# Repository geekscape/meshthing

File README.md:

meshthing
=========

MeshThing module: Hardware and software repository

Current version is v1.2.

Contents:
----------
-Hardware - Source files for PCB production.

-Software - Source files for testing and use.

-Resources - Additional utilities and documentation.

-Reference - Mostly datasheets.

Pinout:

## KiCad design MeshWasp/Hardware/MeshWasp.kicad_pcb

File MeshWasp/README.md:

meshwasp
=========

MeshWasp breakout: Hardware and software repository

This board hosts a meshthing 802.15.4 radio module and brings a selection of pins to an XBee form factor. It also includes a micro-SD card holder, reset switch, and LEDs for power and SCK signaling.

Current version is v1.0

Contents:
----------
-Hardware - Source files for PCB production.

-Resources - Additional utilities and documentation.

Pinout:

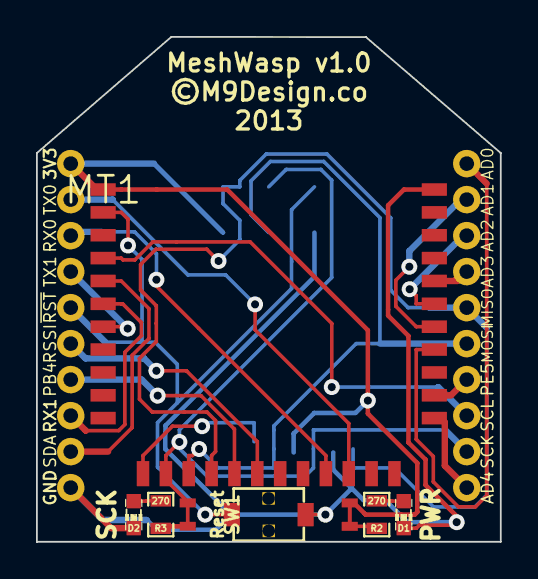
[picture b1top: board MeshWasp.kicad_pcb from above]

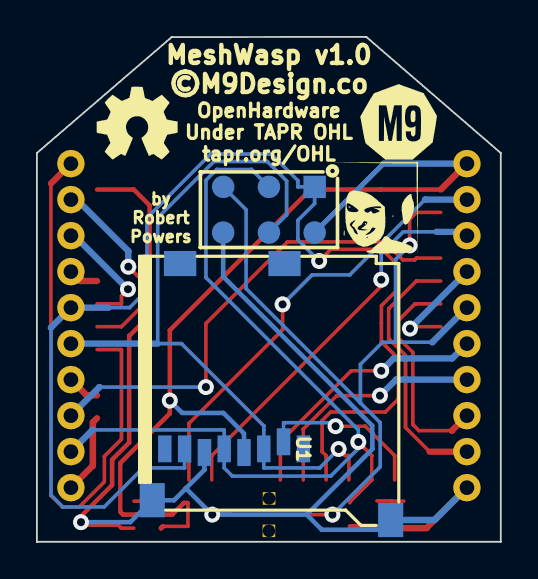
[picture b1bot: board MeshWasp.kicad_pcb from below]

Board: 2 copper layers, 25.8 x 28.1 mm, 14 parts (5 on the bottom side), 25 nets.

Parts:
D1, D2: LED; _MT_LED-0603
G1, G2: LOGO
H2: ICSP; _MC_pin_pad_3x2
MT1: MESHTHING; _MT_CanFootprint-34Pin
R2, R3: 270; _MT_SM0603_Resistor
SJ1, SJ2: SMTJPR; _MW_SMTJumper
SW1: RST; _MT_TC007-TactileSwitch
U1: CONN_MICROSD; _MW_microSD_3M_290805-A
U2: XBEE; _MW_XBee_Board_STD_THPads
VAL: M9Logo-flipped

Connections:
+3.3V: H2.2, MT1.1, SJ1.1, U1.4, U2.1
GND: D1.2, D2.2, H2.6, MT1.34, SW1.2, U1.6, U1.9, U2.10
MISO: H2.1, MT1.15, U1.7, U2.16
MOSI: H2.4, MT1.14, U1.3, U2.15
unnamed: D1.1, R2.2
unnamed: D2.1, R3.2
unnamed: R2.1, SJ1.2
unnamed: R3.1, SJ2.2
PB0/SS: MT1.12, U1.2
PB4: MT1.16, U2.7
PB5: MT1.17, U2.6
PE4: MT1.24, U2.11
PE5: MT1.25, U2.14
PF0: MT1.27, U2.20
PF1: MT1.28, U2.19
PF2: MT1.29, U2.18
PF3-4: MT1.30, U2.17
RX0: MT1.20, U2.3
RX1: MT1.6, U2.8
Reset: H2.5, MT1.2, SW1.1, U2.5
SCK: H2.3, MT1.13, SJ2.1, U1.5, U2.12
SCL: MT1.4, U2.13
SDA: MT1.5, U2.9
TX0: MT1.21, U2.2
TX1: MT1.7, U2.4

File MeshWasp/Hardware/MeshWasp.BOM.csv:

Part	Reference	Value	Package	Manufacturer	MFG. Part No.	Number	Comment	Link	Digikey PartNo.		More Notes/Comments
SMD LED	D1	RED LED	SM0603	Lite-On Inc	LTST-C190KRKT	1	2v/red	http://www.digikey.com/product-detail/en/LTST-C190KRKT/160-1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	160-1436-1-ND		
SMD LED	D2	GREEN LED	SM0603	Lite-On Inc	LTST-C190GKT	1	2v/green	http://www.digikey.com/product-detail/en/LTST-C190GKT/160-11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	160-1183-1-ND		
SMD R	R2/R3	270R	SM0603	Panasonic Electronic Components	ERJ-3GEYJ271V	2	.1W rating	http://www.digikey.com.au/product-detail/en/ERJ-3GEYJ271V/P2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	P270GCT-ND		
Tactile Switch	SW1	Reset	2.9 X 3.9 mm	Well Buying Industrial Co. Ltd.	TC007-BBA	1		http://industry.teema.org.tw/auto/PdtCmpProd_eng.asp?id=2160			2.5mm Tall
uSD Card Connector/Holder	U1	CONN_MICROSD		Amphenol Commercial Products	101-00581-59	1		http://www.digikey.com/product-detail/en/101-00581-59/101-00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	101-00581-59-1-ND		
											
10 Pin 2mm Recepticles	H1/H2	Headers	10 pin x 1 row	SAMTEC	SAMTEC SQT-110-03-L-S	2	Male/female	http://www.samtec.com/ftppub/pdf/sqt_th.pdf

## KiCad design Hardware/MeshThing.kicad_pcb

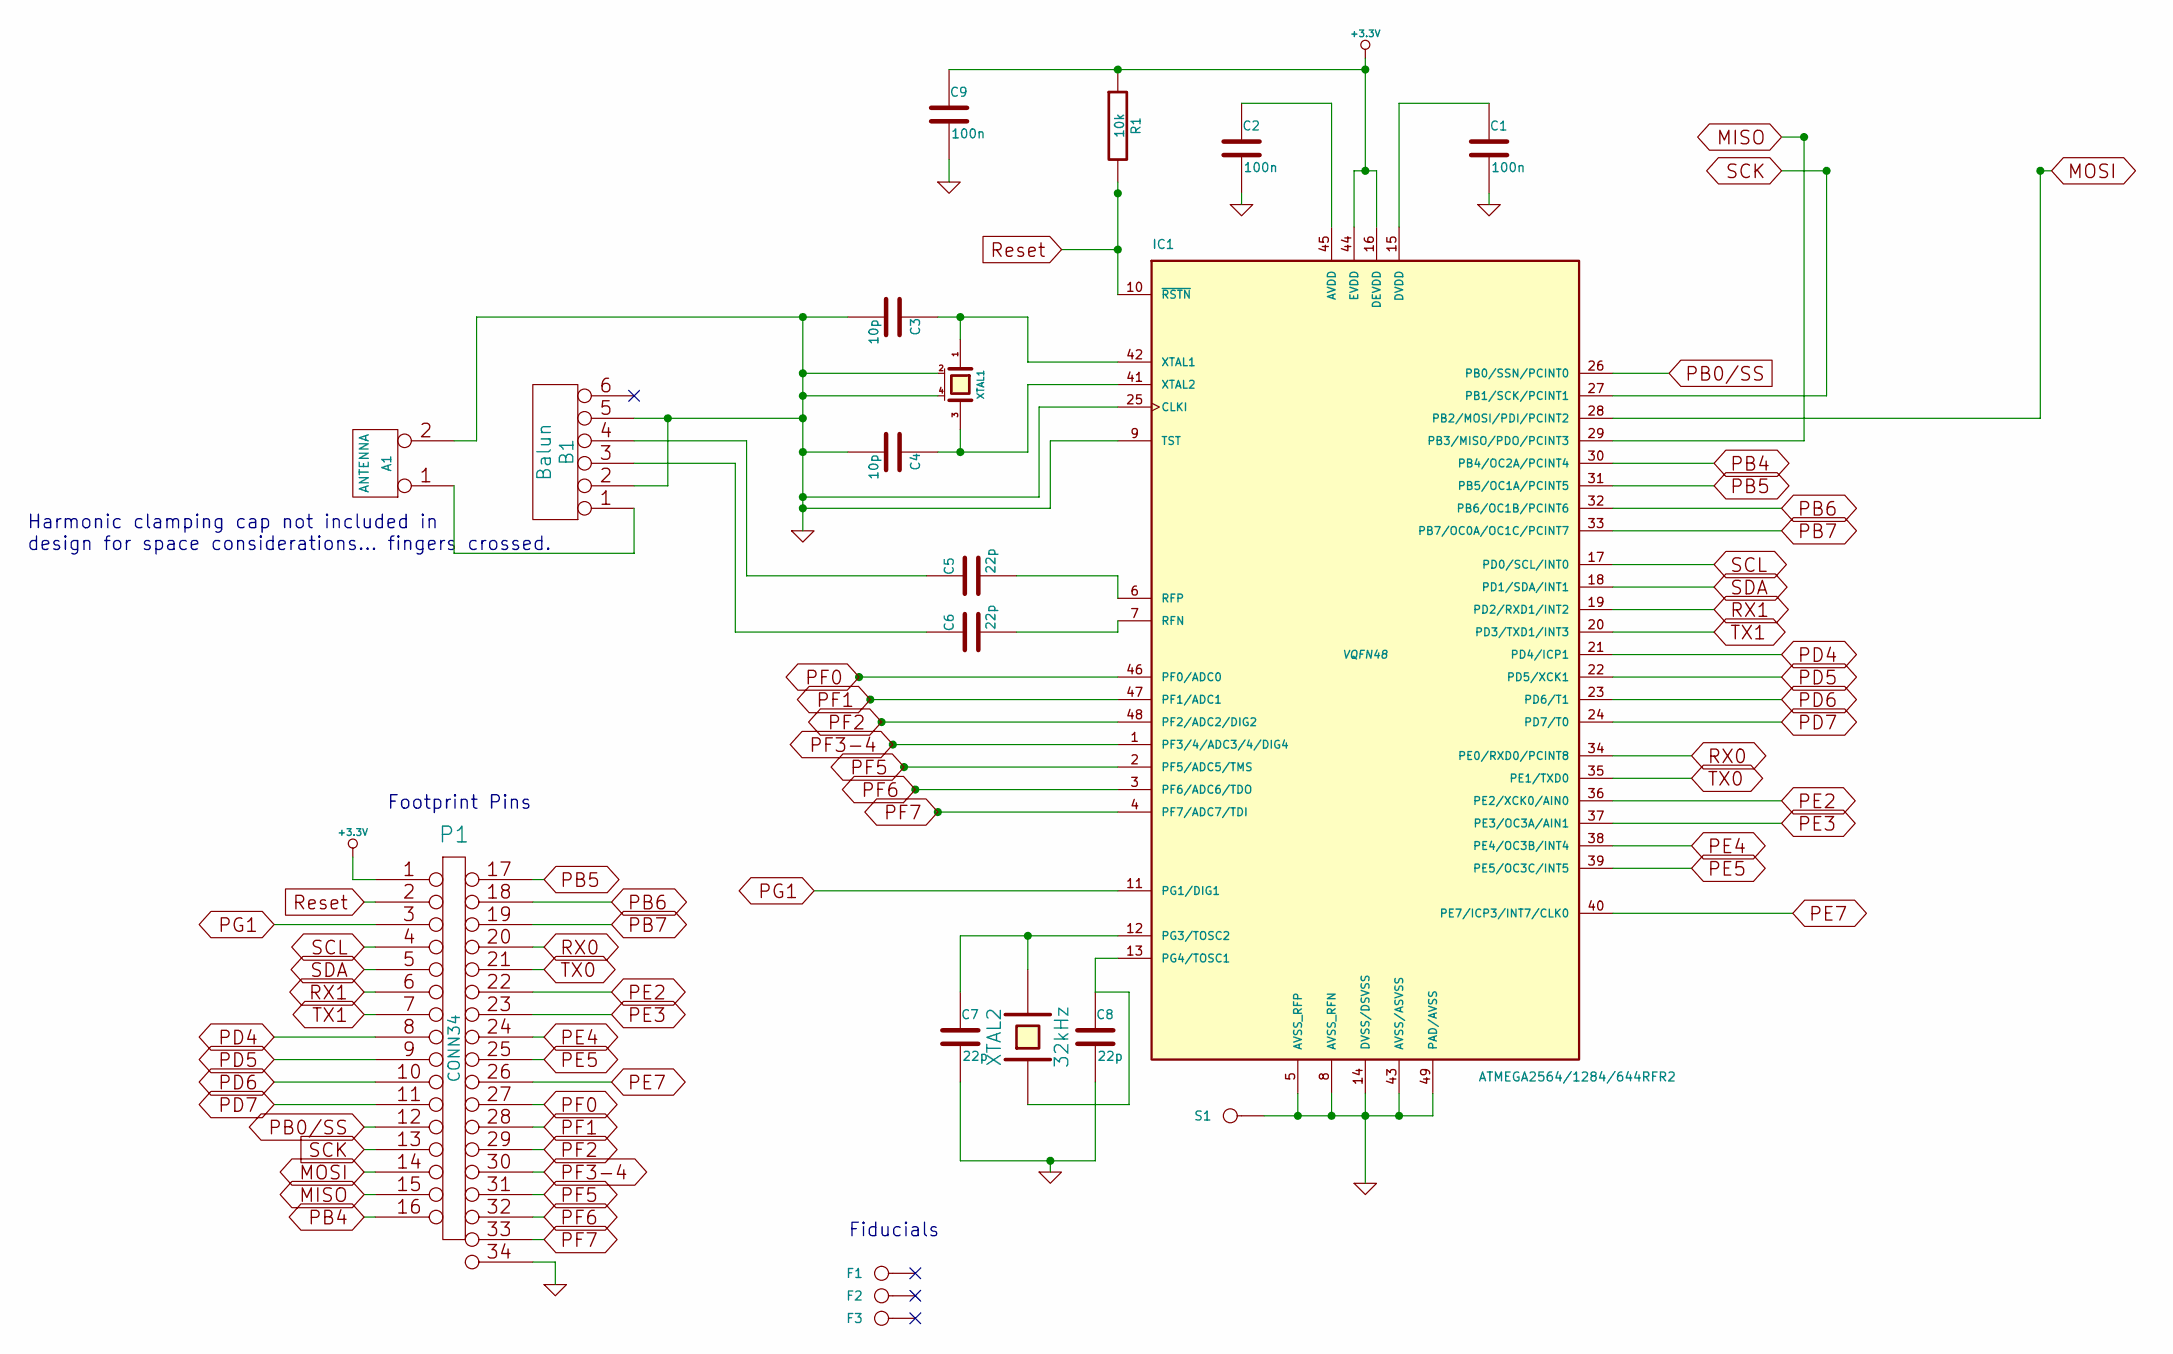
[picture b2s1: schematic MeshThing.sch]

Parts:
A1: ANTENNA
B1: Balun
C1, C2, C9: 100n
C3, C4: 10p
C5, C6, C7, C8: 22p
F1, F2, F3: CONN_1
IC1: ATMEGA2564/1284/644RFR2; VQFN48
P1: CONN34
R1: 10k
S1: RFShield
XTAL1: CRYSTAL_SMD-TSX3225
XTAL2: 32kHz

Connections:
+3.3V: C9.1, IC1.16 (DEVDD), IC1.44 (EVDD), P1.1, R1.1
GND: A1.2 (PM), B1.2, B1.5, C1.2, C2.2, C3.2, C4.2, C7.2, C8.2, C9.2, IC1.5 (AVSS_RFP), IC1.8 (AVSS_RFN), IC1.9 (TST), IC1.14 (DVSS/DSVSS), IC1.25 (CLKI), IC1.43 (AVSS/ASVSS), IC1.49 (PAD/AVSS), P1.34, S1.1, XTAL1.2 (case), XTAL1.4 (case)
MISO: IC1.29 (PB3/MISO/PDO/PCINT3), P1.15
MOSI: IC1.28 (PB2/MOSI/PDI/PCINT2), P1.14
unnamed: A1.1, B1.1
unnamed: B1.3, C6.1
unnamed: B1.4, C5.1
unnamed: C1.1, IC1.15 (DVDD)
unnamed: C2.1, IC1.45 (AVDD)
unnamed: C3.1, IC1.42 (XTAL1), XTAL1.1
unnamed: C4.1, IC1.41 (XTAL2), XTAL1.3
unnamed: C5.2, IC1.6 (RFP)
unnamed: C6.2, IC1.7 (RFN)
unnamed: C7.1, IC1.12 (PG3/TOSC2), XTAL2.2
unnamed: C8.1, IC1.13 (PG4/TOSC1), XTAL2.1
PB0/SS: IC1.26 (PB0/SSN/PCINT0), P1.12
PB4: IC1.30 (PB4/OC2A/PCINT4), P1.16
PB5: IC1.31 (PB5/OC1A/PCINT5), P1.17
PB6: IC1.32 (PB6/OC1B/PCINT6), P1.18
PB7: IC1.33 (PB7/OC0A/OC1C/PCINT7), P1.19
PD4: IC1.21 (PD4/ICP1), P1.8
PD5: IC1.22 (PD5/XCK1), P1.9
PD6: IC1.23 (PD6/T1), P1.10
PD7: IC1.24 (PD7/T0), P1.11
PE2: IC1.36 (PE2/XCK0/AIN0), P1.22
PE3: IC1.37 (PE3/OC3A/AIN1), P1.23
PE4: IC1.38 (PE4/OC3B/INT4), P1.24
PE5: IC1.39 (PE5/OC3C/INT5), P1.25
PE7: IC1.40 (PE7/ICP3/INT7/CLK0), P1.26
PF0: IC1.46 (PF0/ADC0), P1.27
PF1: IC1.47 (PF1/ADC1), P1.28
PF2: IC1.48 (PF2/ADC2/DIG2), P1.29
PF3-4: IC1.1 (PF3/4/ADC3/4/DIG4), P1.30
PF5: IC1.2 (PF5/ADC5/TMS), P1.31
PF6: IC1.3 (PF6/ADC6/TDO), P1.32
PF7: IC1.4 (PF7/ADC7/TDI), P1.33
PG1: IC1.11 (PG1/DIG1), P1.3
RX0: IC1.34 (PE0/RXD0/PCINT8), P1.20
RX1: IC1.19 (PD2/RXD1/INT2), P1.6
Reset: IC1.10 (~RSTN), P1.2, R1.2
SCK: IC1.27 (PB1/SCK/PCINT1), P1.13
SCL: IC1.17 (PD0/SCL/INT0), P1.4
SDA: IC1.18 (PD1/SDA/INT1), P1.5
TX0: IC1.35 (PE1/TXD0), P1.21
TX1: IC1.20 (PD3/TXD1/INT3), P1.7

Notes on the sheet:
Harmonic clamping cap not included in design for space considerations... fingers crossed.
Fiducials
Footprint Pins

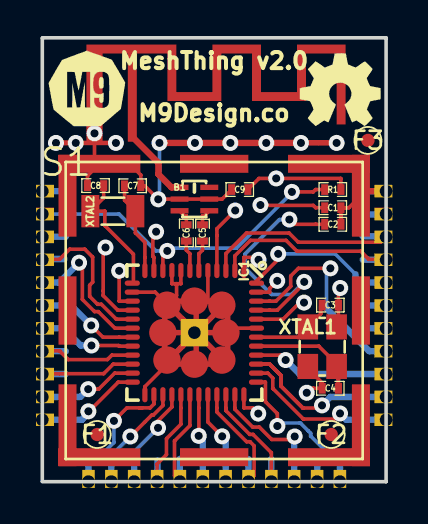
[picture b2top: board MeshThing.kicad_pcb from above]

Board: 4 copper layers, 19.1 x 24.7 mm, 22 parts (1 on the bottom side), 45 nets.

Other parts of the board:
PrettyLady: PrettyLady; _MC_LOGO-PrettyLady
VAL: M9Logo-scaled

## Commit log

2013-09-16 Commit v1.1.
2013-10-15 Begin v1.2. Cleanup done.
2013-10-17 V1.2 nearly done. Alignment marks needed.
2013-10-18 More checks.
2013-10-18 Removing Archive folder from git tracking.
2013-10-18 Removing Ref folder from tracking.
2013-10-18 Untracking folders.
2013-10-18 error.
2013-10-18 Readme.
2013-10-18 Fiducials added, refining positions.
2013-10-22 v1.2 Production.
2013-11-07 Bootloader for >=v1.1.
2013-11-14 Adding back reference documents to repo.
2013-11-14 Remove "*~" files.
2013-11-15 Moving things around and documenting them.
2013-11-15 Update README.
2013-11-15 Updating pins_arduino.h.
2013-11-15 First stab at a pinout poster.
2013-11-15 Somechanges to update Arduion pins.
2013-11-18 First crack at pinout poster.
2013-11-18 Pinout poster changes.
2013-11-18 Pinout .jpg.
2013-11-22 Software changes. Added pin exercise.
2013-11-22 Cleaning up.
2013-12-03 Updating some documentation.
2013-12-03 Reduce size of MTPinout.png
2013-12-05 TAPR Hardware License added.
2013-12-11 Typo on Pinout.
2013-12-11 Initial Firmata support and pins_arduino fixes.
2013-12-22 Final v1.2 commit.
2013-12-22 Initial v2.0 commit.
2013-12-22 README quick update.
2013-12-23 Minor.
2013-12-23 More minor fixes.
2013-12-23 Very nearly there.
2013-12-24 MeshWasp added.
2014-01-08 Logo work and branch to flip.
2014-01-08 Initial flip done.
2014-01-09 Mostly silks and initial documentation.
2014-01-09 Thicken pwr traces, mechanical relief on TH.
2014-01-09 Logo work.
2014-01-15 ICSP keepout recognized on MW. Silks, gerbers.
2014-01-18 Moved ATMega256RFR2 STK500 bootloader to new GitHub repository ... https://github.com/geekscape/stk500boot_atmega256rfr2
2014-01-22 Added some documentation/pinout graphics.
2014-01-24 Minor changes, initial positions file for MT.
2014-02-18 Removed ICSP pads.
2014-02-18 Annyoing files.
2014-02-18 Boards.txt
2014-03-05 Minor silks & logo work.
2014-03-05 Positions file and footprint pad drills to .7mm.
2014-03-05 MeshWasp positions & render.
2014-08-16 Updated some MW documentation.
2014-08-16 MW README.

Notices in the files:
Hardware/MeshThing.kicad_pcb:
© M9Design.co 2013
MeshWasp/Hardware/MeshWasp.kicad_pcb:
©M9Design.co
